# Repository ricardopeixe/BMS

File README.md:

# BMS (Battery Management System)
A BMS desenvolvida terá a exclusiva tarefa de realizar o equilíbrio da bateria implementada,
através de um sistema puramente elétrico. Não existe forma de monitorizar o estado das células, nem gerir
o seu equilíbrio através de firmware, visto o objetivo desta BMS é realizar apenas um carregamento seguro
sem a interferência de meios externos. Existe a possibilidade de continuar a
desenvolver esta BMS, de um modo a trocar de uma operação local, para um sistema acessível via algum
protocolo de comunicação sem fios, o que acrescenta muitas vantagens em termos de monitorização e extração
de dados. Esta possibilidade transforma-se assim num upgrade para trabalho futuro.

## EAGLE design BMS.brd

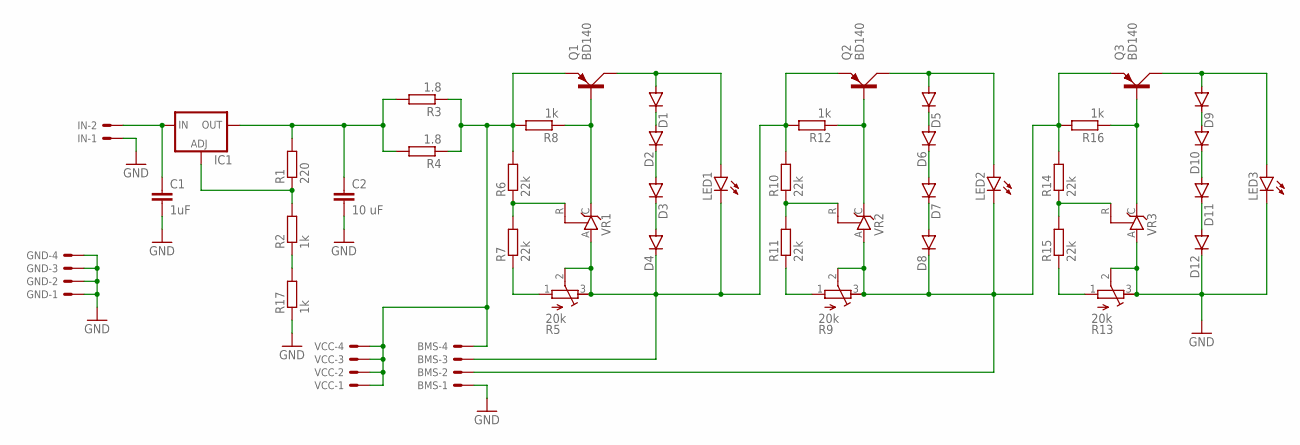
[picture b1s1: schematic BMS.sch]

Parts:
BMS: 22-23-2041
C1: 1uF; C025-025X050
C2: 10 uF; C025-025X050
D1, D2, D3, D4, D5, D6, D7, D8, D9, D10, D11, D12: 1N4004; DO41-10
GND: 22-23-2041
IC1: LM317TS; 317TS
IN: 22-23-2021
LED1, LED2, LED3: LED5MM
Q1, Q2, Q3: BD140; TO126AV
R1: 220; 0207/10
R2, R8, R12, R16, R17: 1k; 0207/10
R3, R4: 1.8; 0617/22
R5, R9, R13: 20k; RTRIM3296W
R6, R7, R10, R11, R14, R15: 22k; 0207/10
VCC: 22-23-2041
VR1, VR2, VR3: TL431CLP; TO92-CLP

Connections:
GND: BMS.1, C1.2, C2.2, D12.C, GND.1, GND.2, GND.3, GND.4, IN.1, LED3.K (C), R13.2 (S), R13.3 (E), R17.1, VR3.A
unnamed: C2.1, IC1.2 (OUT), R1.2, R3.2, R4.2
unnamed: IC1.1 (ADJ), R1.1, R2.2
unnamed: R6.1, R7.2, VR1.R
unnamed: BMS.4, Q1.E, R3.1, R4.1, R6.2, R8.2, VCC.1, VCC.2, VCC.3, VCC.4
unnamed: R5.1 (A), R7.1
unnamed: BMS.3, D4.C, LED1.K (C), Q2.E, R5.2 (S), R5.3 (E), R10.2, R12.2, VR1.A
unnamed: Q1.B, R8.1, VR1.C
unnamed: D1.A, LED1.A, Q1.C
unnamed: D1.C, D2.A
unnamed: D2.C, D3.A
unnamed: D3.C, D4.A
unnamed: C1.1, IC1.3 (IN), IN.2
unnamed: R10.1, R11.2, VR2.R
unnamed: R9.1 (A), R11.1
unnamed: BMS.2, D8.C, LED2.K (C), Q3.E, R9.2 (S), R9.3 (E), R14.2, R16.2, VR2.A
unnamed: Q2.B, R12.1, VR2.C
unnamed: D5.C, D6.A
unnamed: D6.C, D7.A
unnamed: D7.C, D8.A
unnamed: D5.A, LED2.A, Q2.C
unnamed: R2.1, R17.2
unnamed: R14.1, R15.2, VR3.R
unnamed: R13.1 (A), R15.1
unnamed: Q3.B, R16.1, VR3.C
unnamed: D9.C, D10.A
unnamed: D10.C, D11.A
unnamed: D11.C, D12.A
unnamed: D9.A, LED3.A, Q3.C

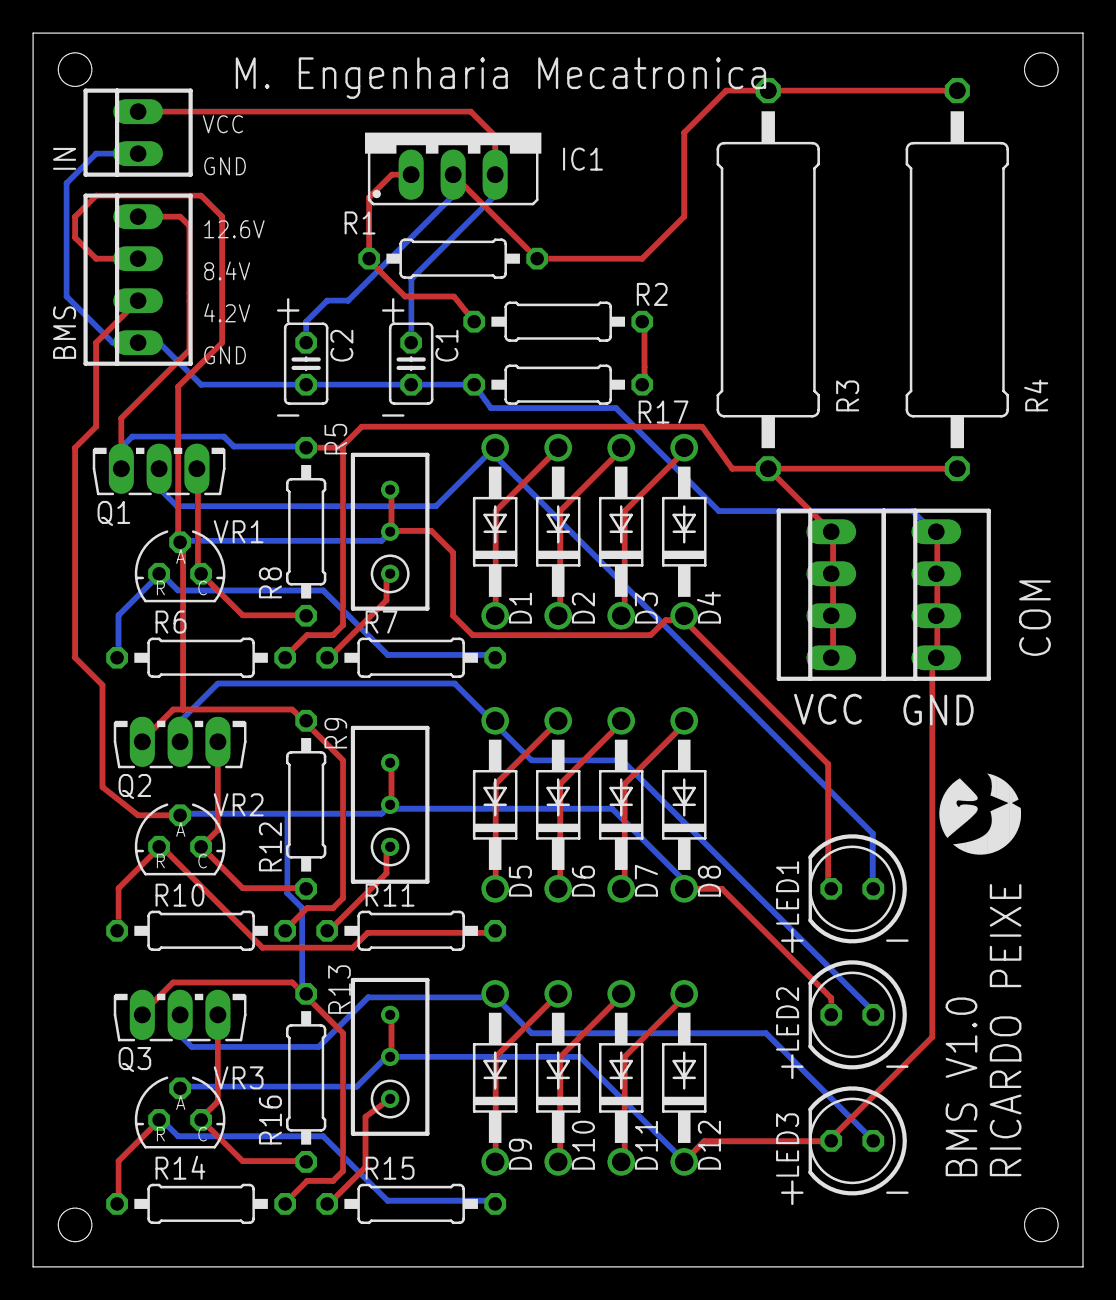
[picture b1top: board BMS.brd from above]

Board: 2 copper layers, 63.5 x 74.6 mm, 45 parts (0 on the bottom side), 29 nets.

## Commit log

2022-04-28 EAGLE Files
2022-04-28 Create Imagens
